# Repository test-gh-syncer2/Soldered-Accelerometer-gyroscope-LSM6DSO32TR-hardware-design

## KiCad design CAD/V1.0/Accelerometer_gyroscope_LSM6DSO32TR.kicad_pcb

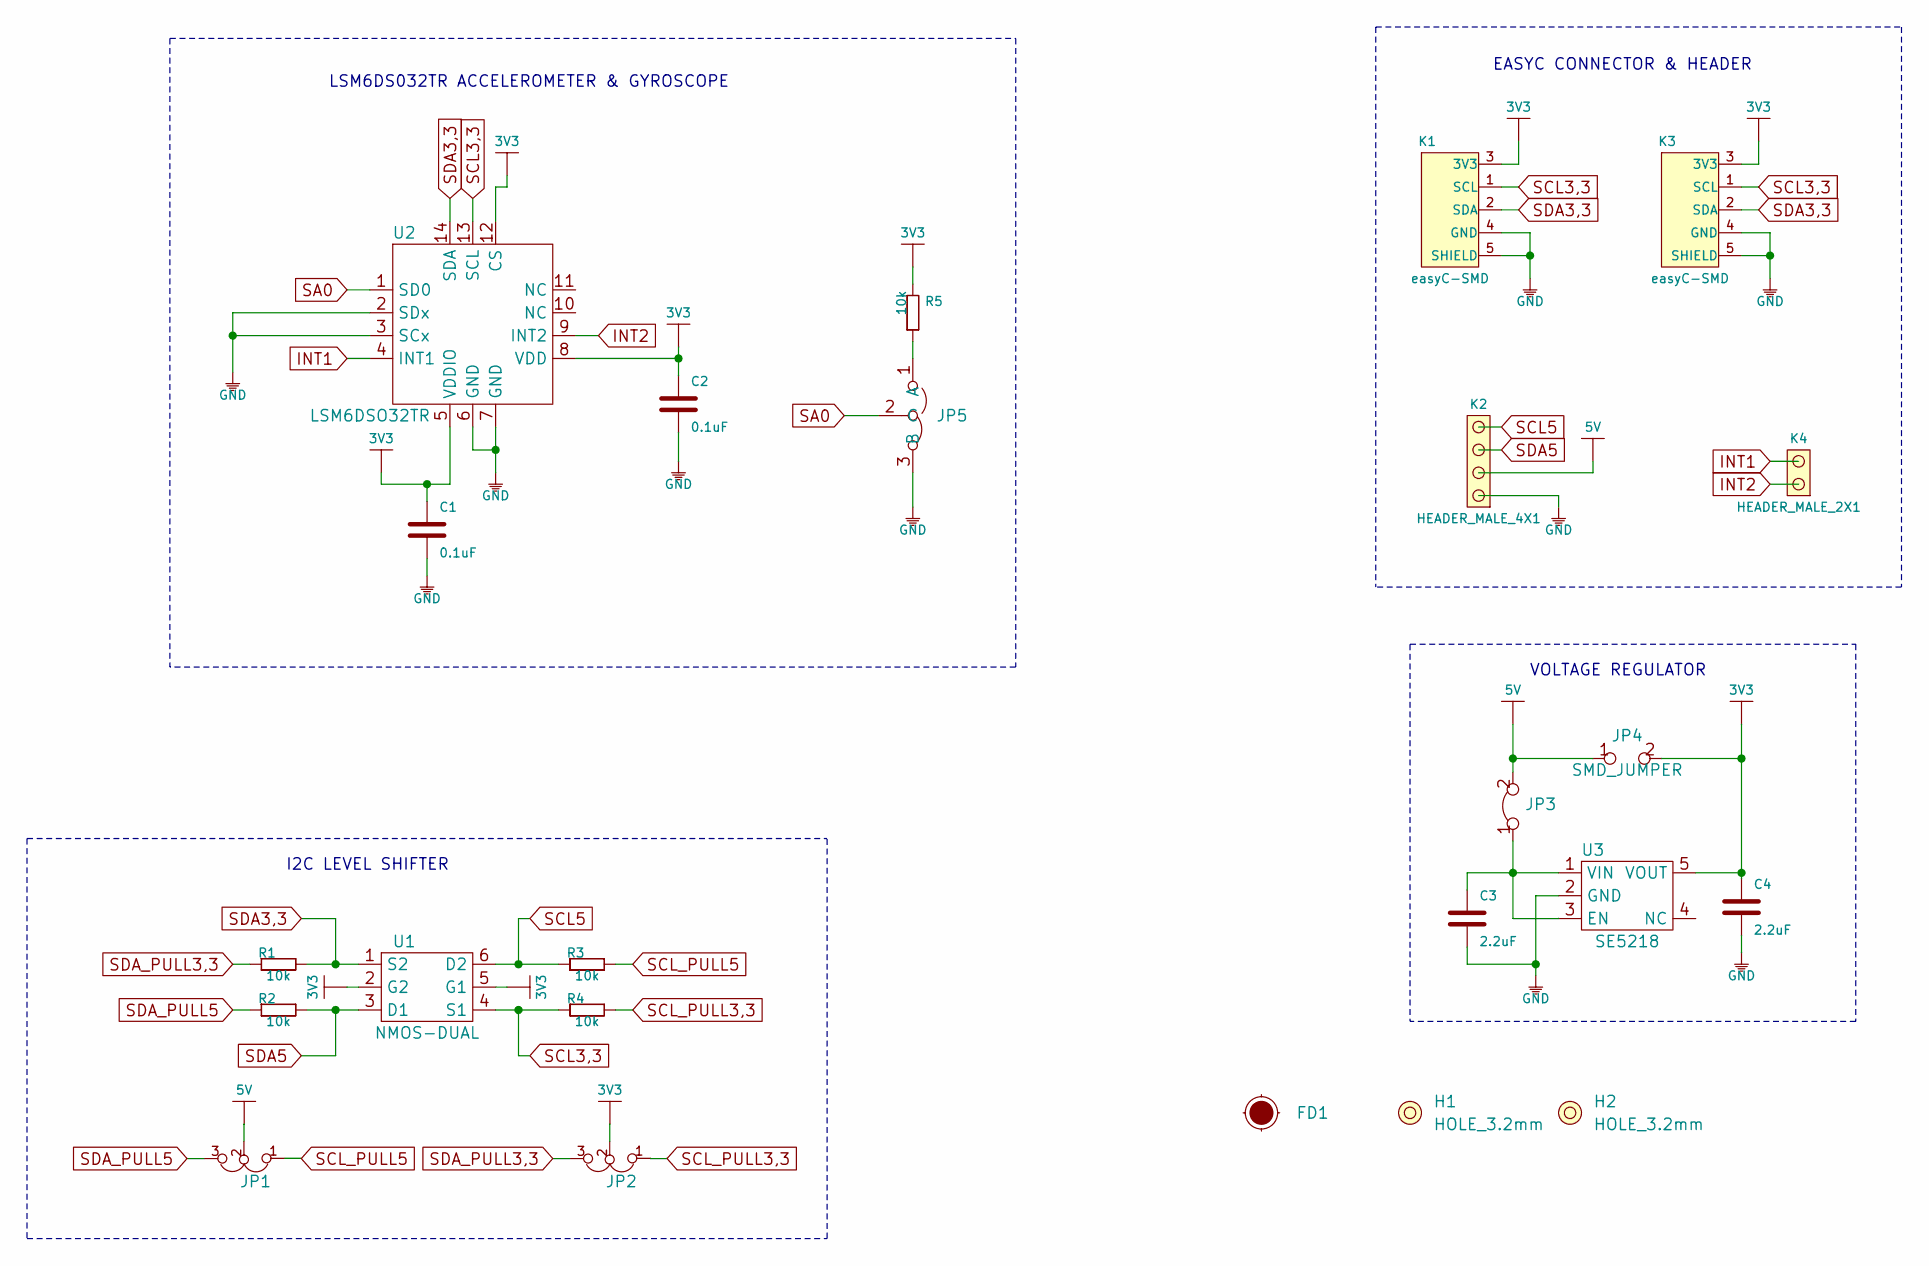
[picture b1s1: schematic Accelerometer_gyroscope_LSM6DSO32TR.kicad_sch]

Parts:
C1, C2: 0.1uF; 0603C
C3, C4: 2.2uF; 0603C
FD1: Fiducial_Stencil; FIDUCIAL_1MM_PASTE
H1, H2: HOLE_3.2mm
JP1, JP2: SMD_JUMPER_3_PAD_TRACE
JP3: SMD-JUMPER-CONNECTED_TRACE_NOSLODERMASK
JP4: SMD_JUMPER
JP5: JUMPER_3_RIGHT; SMD_JUMPER_3_PAD_CONNECTED_RIGHT
K1, K3: easyC-SMD; easyC-connector
K2: HEADER_MALE_4X1
K4: HEADER_MALE_2X1
R1, R2, R3, R4, R5: 10k; 0603R
U1: NMOS-DUAL; SOT-363
U2: LSM6DSO32TR
U3: SE5218; SOT-23-5

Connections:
3V3: C1.2, C2.2, C4.2, JP2.2, JP4.2, K1.3 (3V3), K3.3 (3V3), R5.2, U1.2 (G2), U1.5 (G1), U2.5 (VDDIO), U2.8 (VDD), U2.12 (CS), U3.5 (VOUT)
5V: JP1.2, JP3.2, JP4.1, K2.2
GND: C1.1, C2.1, C3.1, C4.1, JP5.3 (B), K1.4 (GND), K1.5 (SHIELD), K2.1, K3.4 (GND), K3.5 (SHIELD), U2.2 (SDx), U2.3 (SCx), U2.6 (GND), U2.7 (GND), U3.2 (GND)
INT1: K4.2, U2.4 (INT1)
INT2: K4.1, U2.9 (INT2)
unnamed: C3.2, JP3.1, U3.1 (VIN), U3.3 (EN)
unnamed: JP5.1 (A), R5.1
SA0: JP5.2 (C), U2.1 (SD0)
SCL3,3: K1.1 (SCL), K3.1 (SCL), R4.1, U1.4 (S1), U2.13 (SCL)
SCL5: K2.4, R3.1, U1.6 (D2)
SCL_PULL3,3: JP2.1, R4.2
SCL_PULL5: JP1.1, R3.2
SDA3,3: K1.2 (SDA), K3.2 (SDA), R1.2, U1.1 (S2), U2.14 (SDA)
SDA5: K2.3, R2.2, U1.3 (D1)
SDA_PULL3,3: JP2.3, R1.1
SDA_PULL5: JP1.3, R2.1

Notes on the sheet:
I2C LEVEL SHIFTER
LSM6DS032TR ACCELEROMETER & GYROSCOPE
VOLTAGE REGULATOR
EASYC CONNECTOR & HEADER

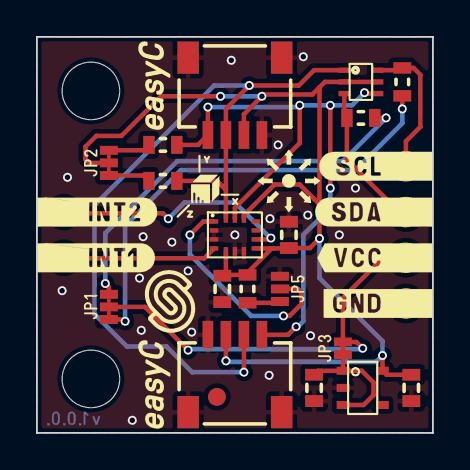
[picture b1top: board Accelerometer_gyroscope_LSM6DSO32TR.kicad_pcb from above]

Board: 2 copper layers, 22.0 x 22.0 mm, 24 parts (1 on the bottom side), 16 nets.

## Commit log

2021-09-23 Syncing to git
2021-09-23 Updating open source files.
